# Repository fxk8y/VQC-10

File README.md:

VQC-10
======

ESP32 Display project featuring VQC-10 displays

**WARNING: This design was never tested actually as I lost focus on the project!**

LICENSE
-------

This project is licensed unser `BSD 2-Clause License`.  
**This includes every file in this repository EXCEPT "VQC10_Funkamateur.pdf" for which I don't have the copyright!**

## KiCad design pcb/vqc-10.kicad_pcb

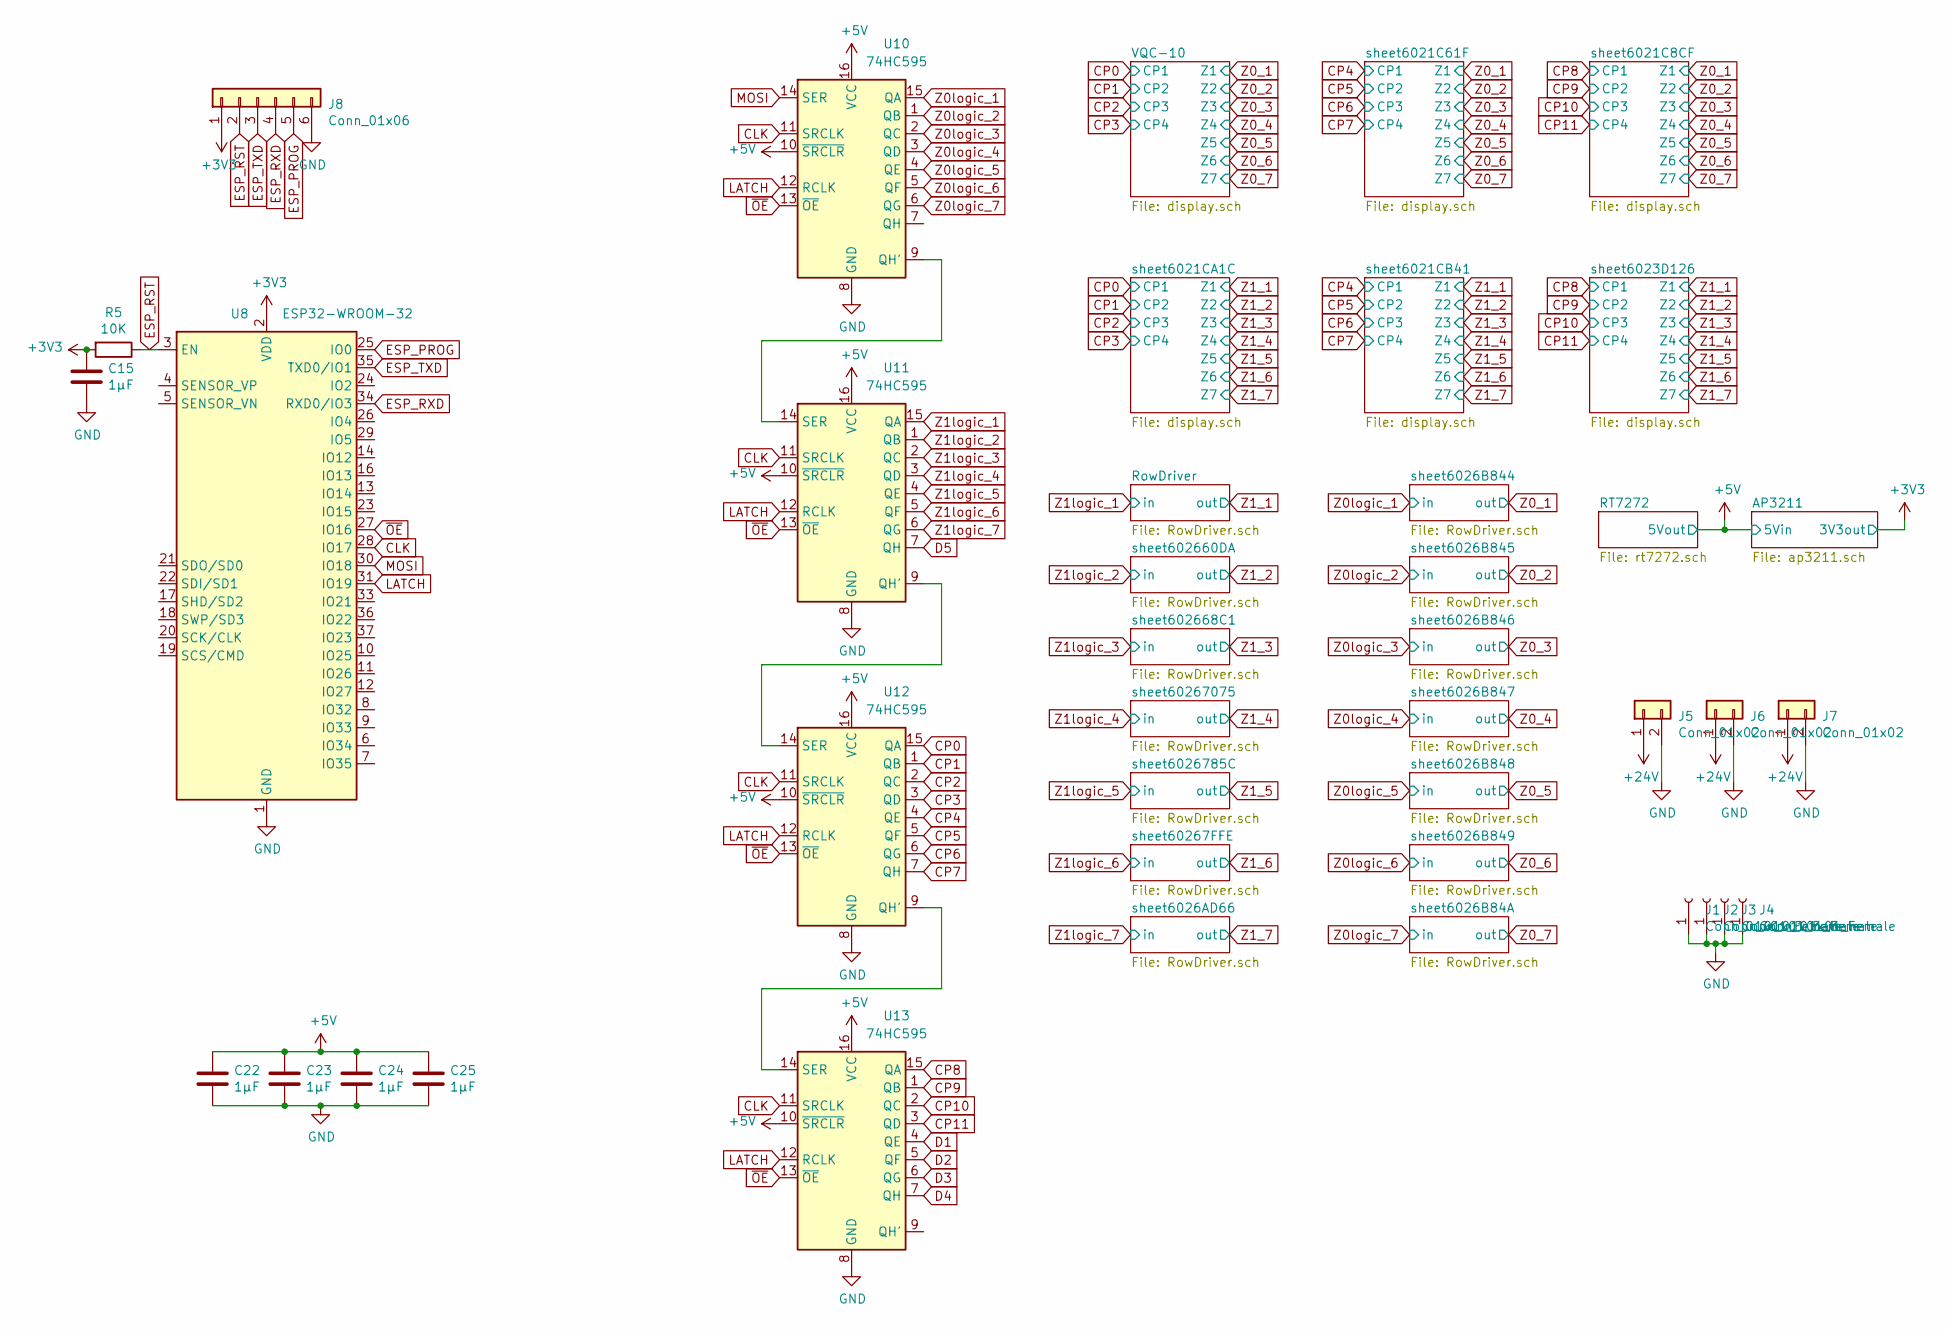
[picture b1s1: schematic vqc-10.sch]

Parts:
C15, C22, C23, C24, C25: 1µF; C_0805_2012Metric_Pad1.15x1.40mm_HandSolder
J1, J2, J3, J4: Conn_01x01_Female; MountingHole_3.2mm_M3_Pad_Via
J5, J6, J7: Conn_01x02; PinHeader254_01x02
J8: Conn_01x06; Micropart-6
R5: 10K; R_0805_2012Metric_Pad1.15x1.40mm_HandSolder
U8: ESP32-WROOM-32
U10, U11, U12, U13: 74HC595; SOIC-16_3.9x9.9mm_P1.27mm

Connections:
+3V3: C15.1, J8.1, R5.2, U8.2 (VDD); also elsewhere on the board
+5V: C22.1, C23.1, C24.1, C25.1, U10.10 (~SRCLR), U10.16 (VCC), U11.10 (~SRCLR), U11.16 (VCC), U12.10 (~SRCLR), U12.16 (VCC), U13.10 (~SRCLR), U13.16 (VCC); also elsewhere on the board
+24V: J5.1, J6.1, J7.1; also elsewhere on the board
CLK: U8.28 (IO17), U10.11 (SRCLK), U11.11 (SRCLK), U12.11 (SRCLK), U13.11 (SRCLK)
CP0: U12.15 (QA); also elsewhere on the board
CP1: U12.1 (QB); also elsewhere on the board
CP2: U12.2 (QC); also elsewhere on the board
CP3: U12.3 (QD); also elsewhere on the board
CP4: U12.4 (QE); also elsewhere on the board
CP5: U12.5 (QF); also elsewhere on the board
CP6: U12.6 (QG); also elsewhere on the board
CP7: U12.7 (QH); also elsewhere on the board
CP8: U13.15 (QA); also elsewhere on the board
CP9: U13.1 (QB); also elsewhere on the board
CP10: U13.2 (QC); also elsewhere on the board
CP11: U13.3 (QD); also elsewhere on the board
D1: U13.4 (QE); also elsewhere on the board
D2: U13.5 (QF); also elsewhere on the board
D3: U13.6 (QG); also elsewhere on the board
D4: U13.7 (QH); also elsewhere on the board
D5: U11.7 (QH); also elsewhere on the board
ESP_PROG: J8.5, U8.25 (IO0)
ESP_RST: J8.2, R5.1, U8.3 (EN)
ESP_RXD: J8.4, U8.34 (RXD0/IO3)
ESP_TXD: J8.3, U8.35 (TXD0/IO1)
GND: C15.2, C22.2, C23.2, C24.2, C25.2, J1.1, J2.1, J3.1, J4.1, J5.2, J6.2, J7.2, J8.6, U8.1 (GND), U8.15 (GND), U8.38 (GND), U8.39 (GND), U10.8 (GND), U11.8 (GND), U12.8 (GND), U13.8 (GND); also elsewhere on the board
LATCH: U8.31 (IO19), U10.12 (RCLK), U11.12 (RCLK), U12.12 (RCLK), U13.12 (RCLK)
MOSI: U8.30 (IO18), U10.14 (SER)
unnamed: U10.9 (QH'), U11.14 (SER)
unnamed: U11.9 (QH'), U12.14 (SER)
unnamed: U12.9 (QH'), U13.14 (SER)
Z0logic_1: U10.15 (QA); also elsewhere on the board
Z0logic_2: U10.1 (QB); also elsewhere on the board
Z0logic_3: U10.2 (QC); also elsewhere on the board
Z0logic_4: U10.3 (QD); also elsewhere on the board
Z0logic_5: U10.4 (QE); also elsewhere on the board
Z0logic_6: U10.5 (QF); also elsewhere on the board
Z0logic_7: U10.6 (QG); also elsewhere on the board
Z1logic_1: U11.15 (QA); also elsewhere on the board
Z1logic_2: U11.1 (QB); also elsewhere on the board
Z1logic_3: U11.2 (QC); also elsewhere on the board
Z1logic_4: U11.3 (QD); also elsewhere on the board
Z1logic_5: U11.4 (QE); also elsewhere on the board
Z1logic_6: U11.5 (QF); also elsewhere on the board
Z1logic_7: U11.6 (QG); also elsewhere on the board
~OE: U8.27 (IO16), U10.13 (~OE), U11.13 (~OE), U12.13 (~OE), U13.13 (~OE)

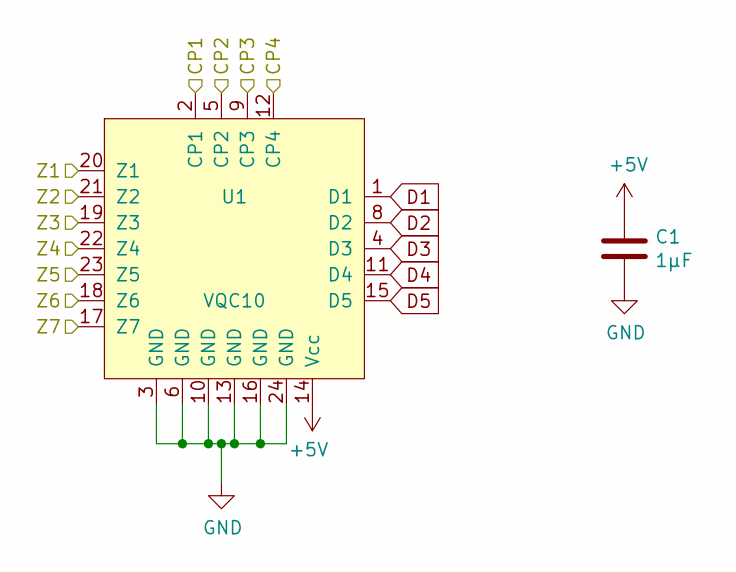
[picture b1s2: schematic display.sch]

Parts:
C1: 1µF; C_0805_2012Metric_Pad1.15x1.40mm_HandSolder
U1: VQC10

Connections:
+5V: C1.1, U1.14 (Vcc); also elsewhere on the board
CP0: U1.2 (CP1); also elsewhere on the board
CP1: U1.5 (CP2); also elsewhere on the board
CP2: U1.9 (CP3); also elsewhere on the board
CP3: U1.12 (CP4); also elsewhere on the board
D1: U1.1 (D1); also elsewhere on the board
D2: U1.8 (D2); also elsewhere on the board
D3: U1.4 (D3); also elsewhere on the board
D4: U1.11 (D4); also elsewhere on the board
D5: U1.15 (D5); also elsewhere on the board
GND: C1.2, U1.3 (GND), U1.6 (GND), U1.10 (GND), U1.13 (GND), U1.16 (GND), U1.24 (GND); also elsewhere on the board
Z0_1: U1.20 (Z1); also elsewhere on the board
Z0_2: U1.21 (Z2); also elsewhere on the board
Z0_3: U1.19 (Z3); also elsewhere on the board
Z0_4: U1.22 (Z4); also elsewhere on the board
Z0_5: U1.23 (Z5); also elsewhere on the board
Z0_6: U1.18 (Z6); also elsewhere on the board
Z0_7: U1.17 (Z7); also elsewhere on the board

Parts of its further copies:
C2, C3, C4, C5, C14: 1µF; C_0805_2012Metric_Pad1.15x1.40mm_HandSolder
U2, U3, U4, U5, U7: VQC10

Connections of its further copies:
+5V: C2.1, C3.1, C4.1, C5.1, C14.1, U2.14 (Vcc), U3.14 (Vcc), U4.14 (Vcc), U5.14 (Vcc), U7.14 (Vcc); also elsewhere on the board
CP0: U4.2 (CP1); also elsewhere on the board
CP1: U4.5 (CP2); also elsewhere on the board
CP2: U4.9 (CP3); also elsewhere on the board
CP3: U4.12 (CP4); also elsewhere on the board
CP4: U2.2 (CP1), U5.2 (CP1); also elsewhere on the board
CP5: U2.5 (CP2), U5.5 (CP2); also elsewhere on the board
CP6: U2.9 (CP3), U5.9 (CP3); also elsewhere on the board
CP7: U2.12 (CP4), U5.12 (CP4); also elsewhere on the board
CP8: U3.2 (CP1), U7.2 (CP1); also elsewhere on the board
CP9: U3.5 (CP2), U7.5 (CP2); also elsewhere on the board
CP10: U3.9 (CP3), U7.9 (CP3); also elsewhere on the board
CP11: U3.12 (CP4), U7.12 (CP4); also elsewhere on the board
D1: U2.1 (D1), U3.1 (D1), U4.1 (D1), U5.1 (D1), U7.1 (D1); also elsewhere on the board
D2: U2.8 (D2), U3.8 (D2), U4.8 (D2), U5.8 (D2), U7.8 (D2); also elsewhere on the board
D3: U2.4 (D3), U3.4 (D3), U4.4 (D3), U5.4 (D3), U7.4 (D3); also elsewhere on the board
D4: U2.11 (D4), U3.11 (D4), U4.11 (D4), U5.11 (D4), U7.11 (D4); also elsewhere on the board
D5: U2.15 (D5), U3.15 (D5), U4.15 (D5), U5.15 (D5), U7.15 (D5); also elsewhere on the board
GND: C2.2, C3.2, C4.2, C5.2, C14.2, U2.3 (GND), U2.6 (GND), U2.10 (GND), U2.13 (GND), U2.16 (GND), U2.24 (GND), U3.3 (GND), U3.6 (GND), U3.10 (GND), U3.13 (GND), U3.16 (GND), U3.24 (GND), U4.3 (GND), U4.6 (GND), U4.10 (GND), U4.13 (GND), U4.16 (GND), U4.24 (GND), U5.3 (GND), U5.6 (GND), U5.10 (GND), U5.13 (GND), U5.16 (GND), U5.24 (GND), U7.3 (GND), U7.6 (GND), U7.10 (GND), U7.13 (GND), U7.16 (GND), U7.24 (GND); also elsewhere on the board
Z0_1: U2.20 (Z1), U3.20 (Z1); also elsewhere on the board
Z0_2: U2.21 (Z2), U3.21 (Z2); also elsewhere on the board
Z0_3: U2.19 (Z3), U3.19 (Z3); also elsewhere on the board
Z0_4: U2.22 (Z4), U3.22 (Z4); also elsewhere on the board
Z0_5: U2.23 (Z5), U3.23 (Z5); also elsewhere on the board
Z0_6: U2.18 (Z6), U3.18 (Z6); also elsewhere on the board
Z0_7: U2.17 (Z7), U3.17 (Z7); also elsewhere on the board
Z1_1: U4.20 (Z1), U5.20 (Z1), U7.20 (Z1); also elsewhere on the board
Z1_2: U4.21 (Z2), U5.21 (Z2), U7.21 (Z2); also elsewhere on the board
Z1_3: U4.19 (Z3), U5.19 (Z3), U7.19 (Z3); also elsewhere on the board
Z1_4: U4.22 (Z4), U5.22 (Z4), U7.22 (Z4); also elsewhere on the board
Z1_5: U4.23 (Z5), U5.23 (Z5), U7.23 (Z5); also elsewhere on the board
Z1_6: U4.18 (Z6), U5.18 (Z6), U7.18 (Z6); also elsewhere on the board
Z1_7: U4.17 (Z7), U5.17 (Z7), U7.17 (Z7); also elsewhere on the board

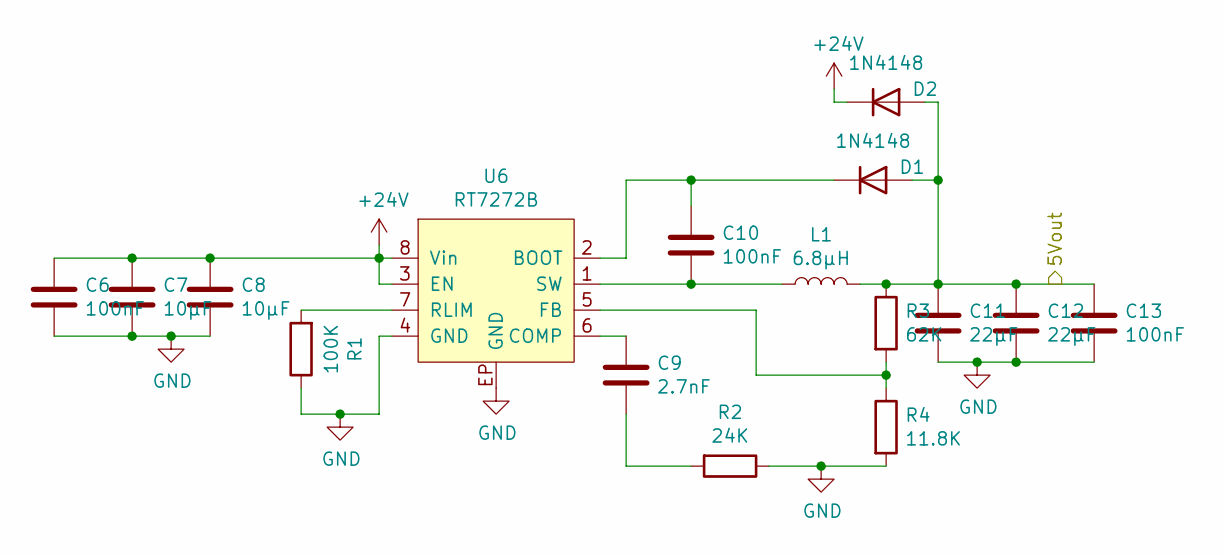
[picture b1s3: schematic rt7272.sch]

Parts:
C6, C10, C13: 100nF; C_0805_2012Metric_Pad1.15x1.40mm_HandSolder
C7, C8: 10µF; C_1206_3216Metric_Pad1.42x1.75mm_HandSolder
C9: 2.7nF; C_0805_2012Metric_Pad1.15x1.40mm_HandSolder
C11, C12: 22µF; C_1210_3225Metric_Pad1.42x2.65mm_HandSolder
D1, D2: 1N4148; D_SOD-123
L1: 6.8µH; MCS0630-6R8MN2
R1: 100K; R_0805_2012Metric_Pad1.15x1.40mm_HandSolder
R2: 24K; R_0805_2012Metric_Pad1.15x1.40mm_HandSolder
R3: 62K; R_0805_2012Metric_Pad1.15x1.40mm_HandSolder
R4: 11.8K; R_0805_2012Metric_Pad1.15x1.40mm_HandSolder
U6: RT7272B; SSOP-8_3.9x5.05mm_P1.27mm_ExposedPad

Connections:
+5V: C11.2, C12.2, C13.2, D1.2 (A), D2.2 (A), L1.2, R3.1; also elsewhere on the board
+24V: C6.2, C7.2, C8.1, D2.1 (K), U6.3 (EN), U6.8 (Vin); also elsewhere on the board
GND: C6.1, C7.1, C8.2, C11.1, C12.1, C13.1, R1.1, R2.1, R4.2, U6.4 (GND), U6.EP (GND); also elsewhere on the board
unnamed: C9.1, R2.2
unnamed: C9.2, U6.6 (COMP)
unnamed: C10.1, D1.1 (K), U6.2 (BOOT)
unnamed: C10.2, L1.1, U6.1 (SW)
unnamed: R1.2, U6.7 (RLIM)
unnamed: R3.2, R4.1, U6.5 (FB)

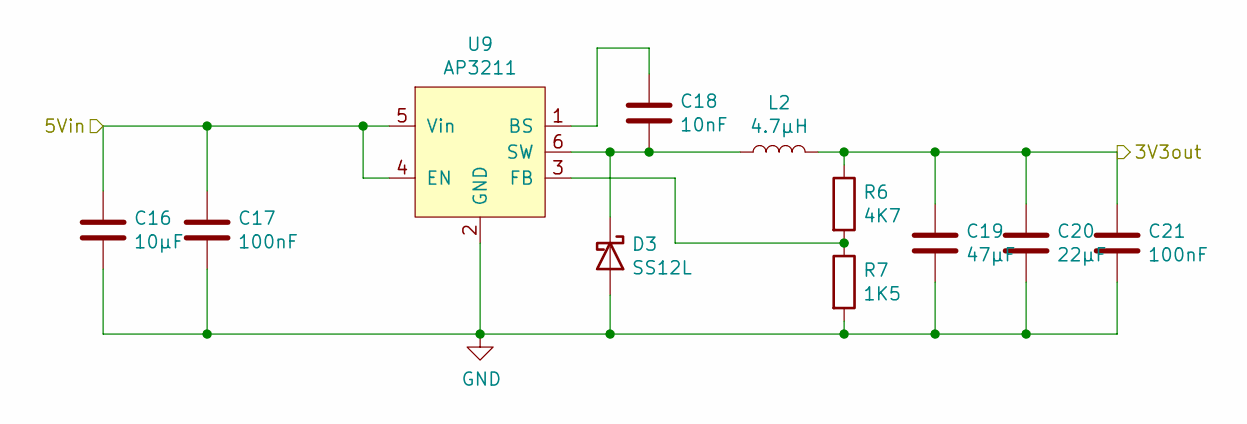
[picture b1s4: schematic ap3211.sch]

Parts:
C16: 10µF; C_1206_3216Metric_Pad1.42x1.75mm_HandSolder
C17, C21: 100nF; C_0805_2012Metric_Pad1.15x1.40mm_HandSolder
C18: 10nF; C_0805_2012Metric_Pad1.15x1.40mm_HandSolder
C19: 47µF; C_1206_3216Metric_Pad1.42x1.75mm_HandSolder
C20: 22µF; C_1206_3216Metric_Pad1.42x1.75mm_HandSolder
D3: SS12L; D_SMA
L2: 4.7µH; L_1008_2520Metric
R6: 4K7; R_0805_2012Metric_Pad1.15x1.40mm_HandSolder
R7: 1K5; R_0805_2012Metric_Pad1.15x1.40mm_HandSolder
U9: AP3211; SOT-23-6_Handsoldering

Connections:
+3V3: C19.1, C20.1, C21.1, L2.2, R6.1; also elsewhere on the board
+5V: C16.1, C17.1, U9.4 (EN), U9.5 (Vin); also elsewhere on the board
GND: C16.2, C17.2, C19.2, C20.2, C21.2, D3.2 (A), R7.2, U9.2 (GND); also elsewhere on the board
unnamed: C18.1, U9.1 (BS)
unnamed: C18.2, D3.1 (K), L2.1, U9.6 (SW)
unnamed: R6.2, R7.1, U9.3 (FB)

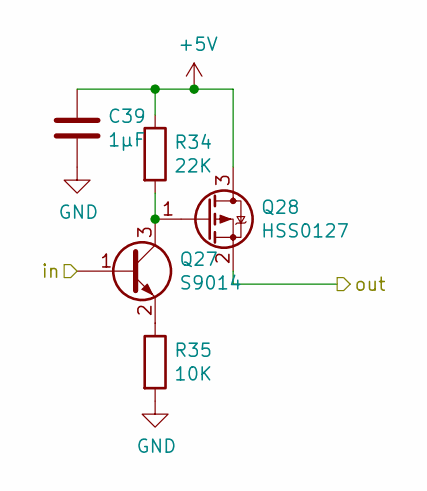
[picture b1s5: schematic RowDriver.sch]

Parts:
C26: 1µF; C_0805_2012Metric_Pad1.15x1.40mm_HandSolder
Q1: S9014; SOT-23
Q2: HSS0127; SOT-23
R8: 22K; R_0805_2012Metric_Pad1.15x1.40mm_HandSolder
R9: 10K; R_0805_2012Metric_Pad1.15x1.40mm_HandSolder

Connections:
+5V: C26.1, Q2.3 (D), R8.1; also elsewhere on the board
GND: C26.2, R9.2; also elsewhere on the board
unnamed: Q1.2 (E), R9.1
unnamed: Q1.3 (C), Q2.1 (G), R8.2
Z1_1: Q2.2 (S); also elsewhere on the board
Z1logic_1: Q1.1 (B); also elsewhere on the board

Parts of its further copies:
C27, C28, C29, C30, C31, C32, C33, C34, C35, C36, C37, C38, C39: 1µF; C_0805_2012Metric_Pad1.15x1.40mm_HandSolder
Q3, Q5, Q7, Q9, Q11, Q13, Q15, Q17, Q19, Q21, Q23, Q25, Q27: S9014; SOT-23
Q4, Q6, Q8, Q10, Q12, Q14, Q16, Q18, Q20, Q22, Q24, Q26, Q28: HSS0127; SOT-23
R10, R12, R14, R16, R18, R20, R22, R24, R26, R28, R30, R32, R34: 22K; R_0805_2012Metric_Pad1.15x1.40mm_HandSolder
R11, R13, R15, R17, R19, R21, R23, R25, R27, R29, R31, R33, R35: 10K; R_0805_2012Metric_Pad1.15x1.40mm_HandSolder

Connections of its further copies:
+5V: C27.1, C28.1, C29.1, C30.1, C31.1, C32.1, C33.1, C34.1, C35.1, C36.1, C37.1, C38.1, C39.1, Q4.3 (D), Q6.3 (D), Q8.3 (D), Q10.3 (D), Q12.3 (D), Q14.3 (D), Q16.3 (D), Q18.3 (D), Q20.3 (D), Q22.3 (D), Q24.3 (D), Q26.3 (D), Q28.3 (D), R10.1, R12.1, R14.1, R16.1, R18.1, R20.1, R22.1, R24.1, R26.1, R28.1, R30.1, R32.1, R34.1; also elsewhere on the board
GND: C27.2, C28.2, C29.2, C30.2, C31.2, C32.2, C33.2, C34.2, C35.2, C36.2, C37.2, C38.2, C39.2, R11.2, R13.2, R15.2, R17.2, R21.2, R23.2, R25.2, R27.2, R29.2, R31.2, R33.2, R35.2; also elsewhere on the board
unnamed: Q3.2 (E), R11.1
unnamed: Q3.3 (C), Q4.1 (G), R10.2
unnamed: Q5.2 (E), R13.1
unnamed: Q5.3 (C), Q6.1 (G), R12.2
unnamed: Q7.2 (E), R15.1
unnamed: Q7.3 (C), Q8.1 (G), R14.2
unnamed: Q9.2 (E), R17.1
unnamed: Q9.3 (C), Q10.1 (G), R16.2
unnamed 44: Q11.2 (E); also elsewhere on the board
unnamed: Q11.3 (C), Q12.1 (G), R18.2
unnamed: Q13.2 (E), R21.1
unnamed: Q13.3 (C), Q14.1 (G), R20.2
unnamed: Q15.2 (E), R23.1
unnamed: Q15.3 (C), Q16.1 (G), R22.2
unnamed: Q17.2 (E), R25.1
unnamed: Q17.3 (C), Q18.1 (G), R24.2
unnamed: Q19.2 (E), R27.1
unnamed: Q19.3 (C), Q20.1 (G), R26.2
unnamed: Q21.2 (E), R29.1
unnamed: Q21.3 (C), Q22.1 (G), R28.2
unnamed: Q23.2 (E), R31.1
unnamed: Q23.3 (C), Q24.1 (G), R30.2
unnamed: Q25.2 (E), R33.1
unnamed: Q25.3 (C), Q26.1 (G), R32.2
unnamed: Q27.2 (E), R35.1
unnamed: Q27.3 (C), Q28.1 (G), R34.2
Z0_1: Q16.2 (S); also elsewhere on the board
Z0_2: Q18.2 (S); also elsewhere on the board
Z0_3: Q20.2 (S); also elsewhere on the board
Z0_4: Q22.2 (S); also elsewhere on the board
Z0_5: Q24.2 (S); also elsewhere on the board
Z0_6: Q26.2 (S); also elsewhere on the board
Z0_7: Q28.2 (S); also elsewhere on the board
Z0logic_1: Q15.1 (B); also elsewhere on the board
Z0logic_2: Q17.1 (B); also elsewhere on the board
Z0logic_3: Q19.1 (B); also elsewhere on the board
Z0logic_4: Q21.1 (B); also elsewhere on the board
Z0logic_5: Q23.1 (B); also elsewhere on the board
Z0logic_6: Q25.1 (B); also elsewhere on the board
Z0logic_7: Q27.1 (B); also elsewhere on the board
Z1_2: Q4.2 (S); also elsewhere on the board
Z1_3: Q6.2 (S); also elsewhere on the board
Z1_4: Q8.2 (S); also elsewhere on the board
Z1_5: Q10.2 (S); also elsewhere on the board
Z1_6: Q12.2 (S); also elsewhere on the board
Z1_7: Q14.2 (S); also elsewhere on the board
Z1logic_2: Q3.1 (B); also elsewhere on the board
Z1logic_3: Q5.1 (B); also elsewhere on the board
Z1logic_4: Q7.1 (B); also elsewhere on the board
Z1logic_5: Q9.1 (B); also elsewhere on the board
Z1logic_6: Q11.1 (B); also elsewhere on the board
Z1logic_7: Q13.1 (B); also elsewhere on the board

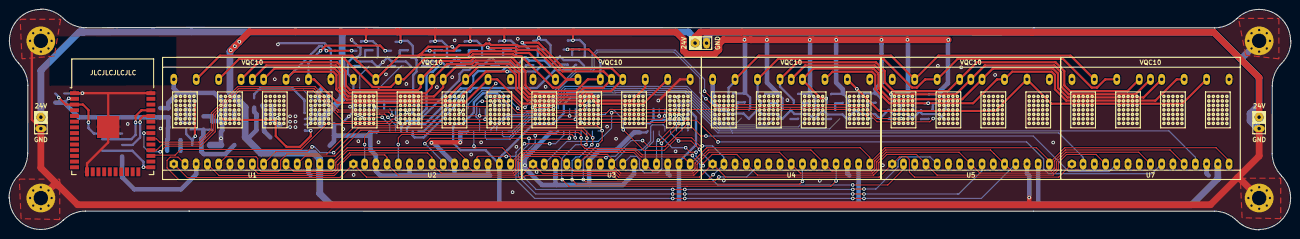
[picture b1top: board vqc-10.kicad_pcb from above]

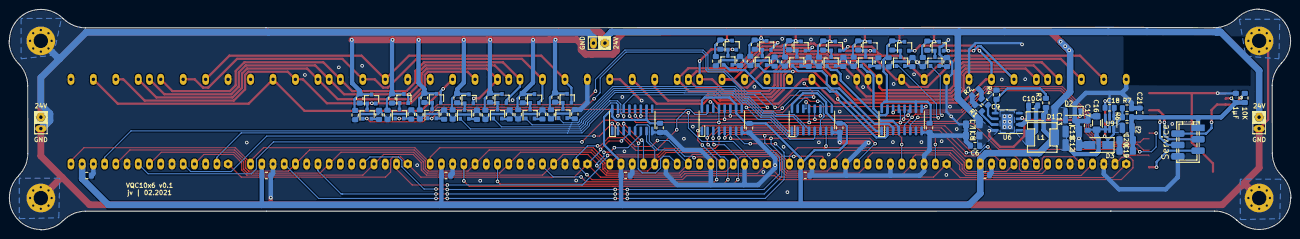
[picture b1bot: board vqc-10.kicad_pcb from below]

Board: 2 copper layers, 285.4 x 49.1 mm, 128 parts (114 on the bottom side), 97 nets.

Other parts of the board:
e: 10K; R_0805_2012Metric_Pad1.15x1.40mm_HandSolder

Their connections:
GND: e.2; also elsewhere on the board
unnamed 44: e.1; also elsewhere on the board
